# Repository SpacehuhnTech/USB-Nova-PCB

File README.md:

# USB-Nova-PCB
USB Nova Hardware Design Files

USB Nova is a cute little USB “drive” that acts as a keyboard, much like the USB Rubber Ducky, WiFi Duck, and other BadUSBs.

Learn about the Project at [usbnova.com](https://usbnova.com).  
Buy one at [spacehuhn.store](https://spacehuhn.store/products/usb-nova).

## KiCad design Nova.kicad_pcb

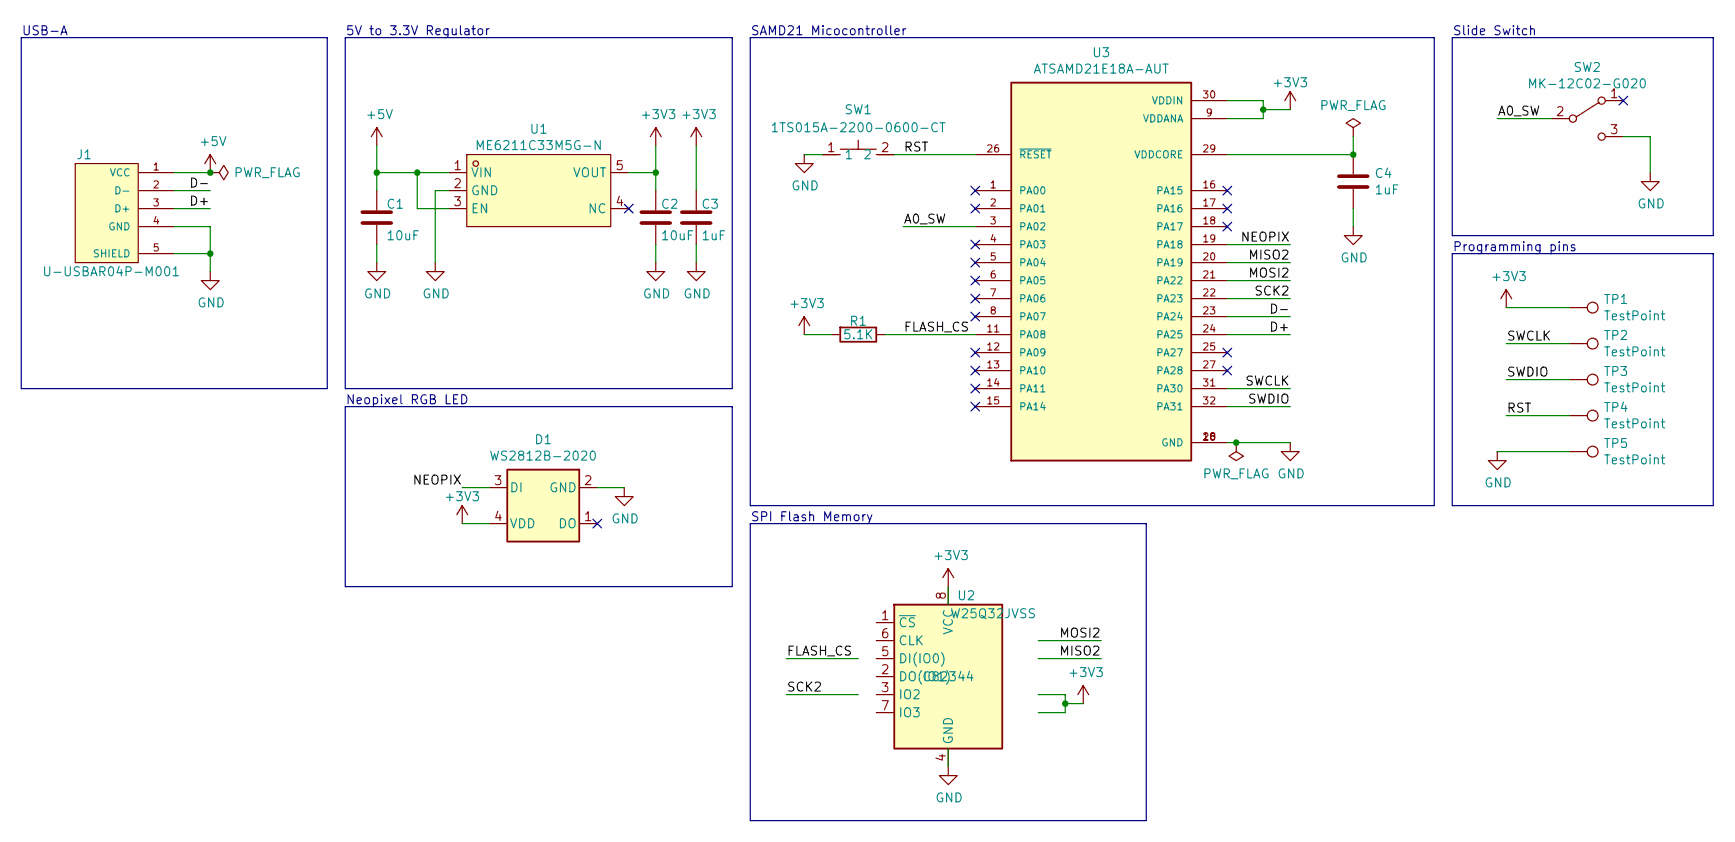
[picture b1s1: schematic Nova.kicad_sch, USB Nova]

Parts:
C1, C2: 10uF; C_0603_1608Metric
C3, C4: 1uF; C_0603_1608Metric
D1: WS2812B-2020; LED-SMD_4P-L2.0-W2.0-TL_WS2812B-2020; Part# WS2812B-2020; LCSC# C965555
J1: U-USBAR04P-M001; USB-A_Plug_THT_U-USBAR04P-M001; Part# U-USBAR04P-M001
R1: 5.1K; R_0603_1608Metric
SW1: 1TS015A-2200-0600-CT; SW-SMD_L3.0-W2.0-LS3.5; MPN C398748; LCSC Part C398748
SW2: MK-12C02-G020; SW_MK-12C02-G020; MPN C963206; LCSC# C963206
TP1, TP2, TP3, TP4, TP5: TestPoint; TestPoint_Pad_D1.5mm
U1: ME6211C33M5G-N; SOT-25-5_ME6211C33M5G; MPN C82942; LCSC# C82942
U2: W25Q32JVSS; SOIC-8_5.23x5.23mm_P1.27mm; MPN C82344
U3: ATSAMD21E18A-AUT; Part# ATSAMD21E18A-AU; Mouser# 556-ATSAMD21E18A-AU

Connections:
+3V3: C2.1, C3.1, D1.4 (VDD), R1.2, TP1.1, U1.5 (VOUT), U2.8 (VCC), U3.9 (VDDANA), U3.30 (VDDIN)
+5V: C1.1, J1.1 (VCC), U1.1 (VIN), U1.3 (EN)
/A0_SW: SW2.2 (B), U3.3 (PA02)
/D+: J1.3 (D+), U3.24 (PA25)
/D-: J1.2 (D-), U3.23 (PA24)
/FLASH_CS: R1.1, U3.11 (PA08)
/MISO2: U3.20 (PA19)
/MOSI2: U3.21 (PA22)
/NEOPIX: D1.3 (DI), U3.19 (PA18)
/RST: SW1.2, TP4.1, U3.26 (~RESET)
/SCK2: U3.22 (PA23)
/SWCLK: TP2.1, U3.31 (PA30)
/SWDIO: TP3.1, U3.32 (PA31)
GND: C1.2, C2.2, C3.2, C4.2, D1.2 (GND), J1.4 (GND), J1.5 (SHIELD), SW1.1, SW2.3 (C), TP5.1, U1.2 (GND), U2.4 (GND), U3.10 (GND), U3.28 (GND)
unnamed: C4.1, U3.29 (VDDCORE)

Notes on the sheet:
Neopixel RGB LED
USB-A
SAMD21 Micocontroller
Slide Switch
Programming pins
5V to 3.3V Regulator
SPI Flash Memory

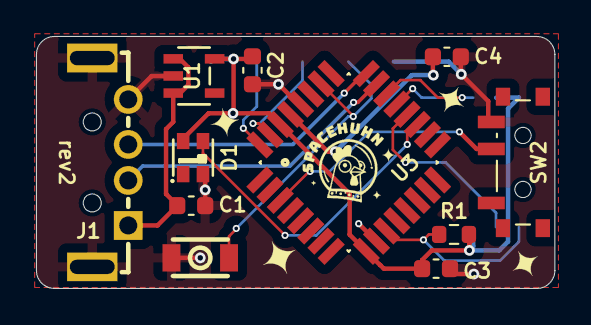
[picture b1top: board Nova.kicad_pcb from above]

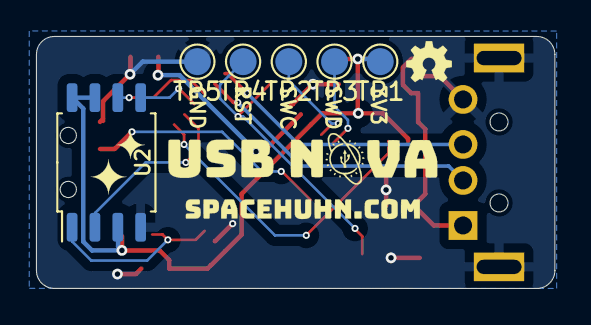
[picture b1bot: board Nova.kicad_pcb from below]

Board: 2 copper layers, 28.8 x 14.0 mm, 17 parts (6 on the bottom side), 12 nets.

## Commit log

2023-03-18 Added files
2023-03-18 Create LICENSE
